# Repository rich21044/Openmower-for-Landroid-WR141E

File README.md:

# Openmower-for-Landroid-WR141E
Taking the hardware developed as part of ClemensElfleins work on Openmower and adapting it to fit a 2019 Landroid WR141E.

This is my first venture into Github so it might get a bit clunky. 
Usual rules apply.. please try to be constructive, I'm learning as I go so if you're going to leave some negative feedback have the grace to tell me why and how I can put it right.

The Openmower project by ClemensElflein started all this for me and I've been so fed up with the performance (or lack thereof) of my Landroid WR141E that I considered selling it and then just buying his kit
however, the Landroid does have cut to edge capability that the Open mower doesnt have and when all is said and done it probably works out at about the same cost.

According to the Gurus on Discord, the firmware in the Landroid is encoded, the data streams between the processors is encoded, the main processor is read locked and the JTAG interface is disabled.
I dont have the knowledge, expertise or equipment to hack into the exiitng Landroid hardware so the plan is to make best use of the Openmower hardware and firmware thats already been developed 
and port it into the Landroid WR141E.

The main thrust of this first stage of the project is to adjust the Openmower motherboard to fit into the available space in the Landroid.

I am also discussing development and asking questions on Discord as @Slartibartfast

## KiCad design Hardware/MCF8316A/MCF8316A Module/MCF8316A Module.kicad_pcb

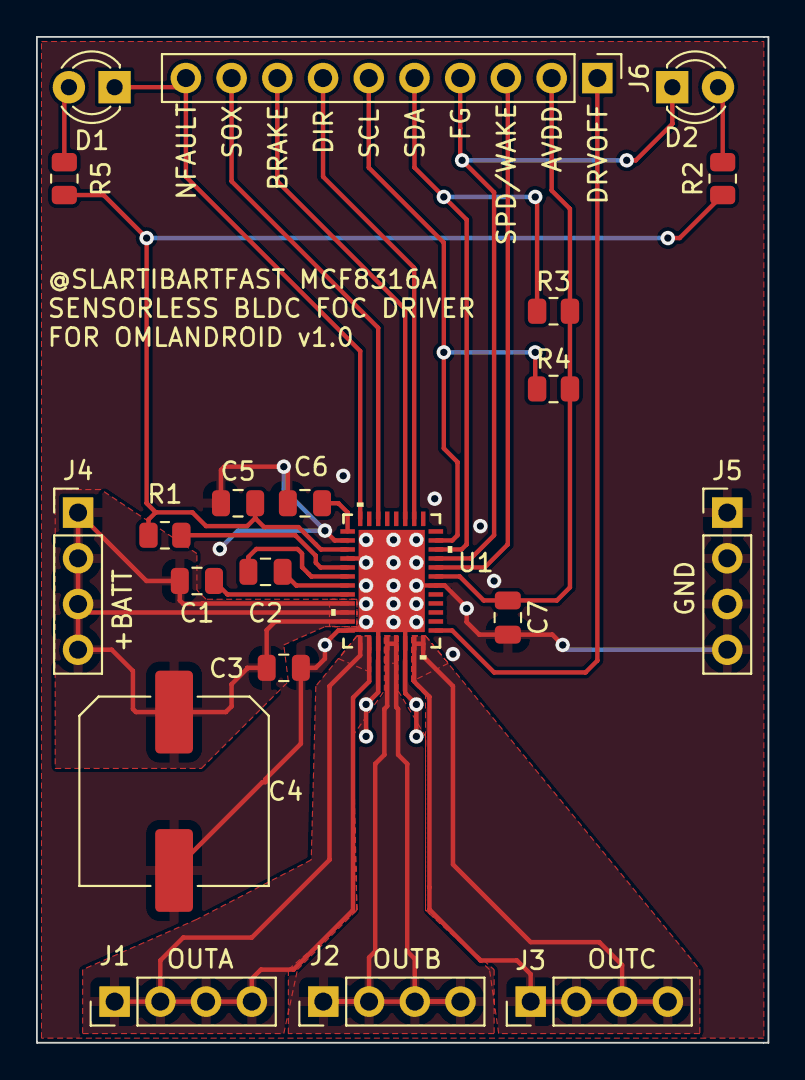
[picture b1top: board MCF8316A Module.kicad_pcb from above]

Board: 2 copper layers, 40.6 x 55.9 mm, 21 parts (0 on the bottom side), 23 nets.

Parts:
C1: 1uF 50v; C_0805_2012Metric
C2: 47nF 50V; C_0805_2012Metric
C3: 0.1uf 50v; C_0805_2012Metric
C4: 330uf 50v; C_Elec_10x10.2
C5: 22uF 10v; C_0805_2012Metric
C6: 1uF 6.3V; C_0805_2012Metric
C7: 1uF 6.3v; C_0805_2012Metric
D1: 3mm Red; LED_D3.0mm
D2: 3mm Grn; LED_D3.0mm
J1, J2, J3, J4, J5: Conn_01x04_Pin; PinHeader_1x04_P2.54mm_Vertical
J6: Conn_01x10_Pin; PinHeader_1x10_P2.54mm_Vertical
R1: 22R; R_0805_2012Metric
R2: 1.54k; R_0805_2012Metric
R3, R4: 5k; R_0805_2012Metric
R5: 1.6k; R_0805_2012Metric
U1: MCF8316A1VRGFR; VQFN40_RGF_TEX

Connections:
+BATT: C1.1, C3.1, C4.1, J4.1, J4.2, J4.3, J4.4, U1.9 (VM), U1.10 (VM), U1.11 (VM)
GND: C3.2, C4.2, C5.2, C6.2, C7.2, J5.1, J5.2, J5.3, J5.4, U1.2 (DGND), U1.4 (GND_BK), U1.12 (PGND), U1.15 (PGND), U1.18 (PGND), U1.26 (AGND), U1.41 (GND)
unnamed: D1.2 (A), R5.2
unnamed: D1.1 (K), J6.10, U1.40 (NFAULT)
unnamed: D2.2 (A), R2.2
unnamed: D2.1 (K), J6.4, U1.29 (FG)
unnamed: J1.1, J1.2, J1.3, J1.4, U1.13 (OUTA), U1.14 (OUTA)
unnamed: J2.1, J2.2, J2.3, J2.4, U1.16 (OUTB), U1.17 (OUTB)
unnamed: J3.1, J3.2, J3.3, J3.4, U1.19 (OUTC), U1.20 (OUTC)
unnamed: J6.1, U1.21 (DRVOFF)
unnamed: C7.1, J6.2, R3.2, R4.2, U1.27 (AVDD)
unnamed: J6.3, U1.28 (SPEED/WAKE)
unnamed: J6.5, R3.1, U1.30 (SDA)
unnamed: J6.6, R4.1, U1.31 (SCL)
unnamed: J6.7, U1.34 (DIR)
unnamed: J6.8, U1.35 (BRAKE)
unnamed: J6.9, U1.38 (SOX)
unnamed: C1.2, U1.8 (CP)
unnamed: C2.1, U1.7 (CPH)
unnamed: C2.2, U1.6 (CPL)
unnamed: C6.1, U1.1 (DVDD)
unnamed: C5.1, R1.1, R2.1, R5.1, U1.3 (FB_BK)
unnamed: R1.2, U1.5 (SW_BK)

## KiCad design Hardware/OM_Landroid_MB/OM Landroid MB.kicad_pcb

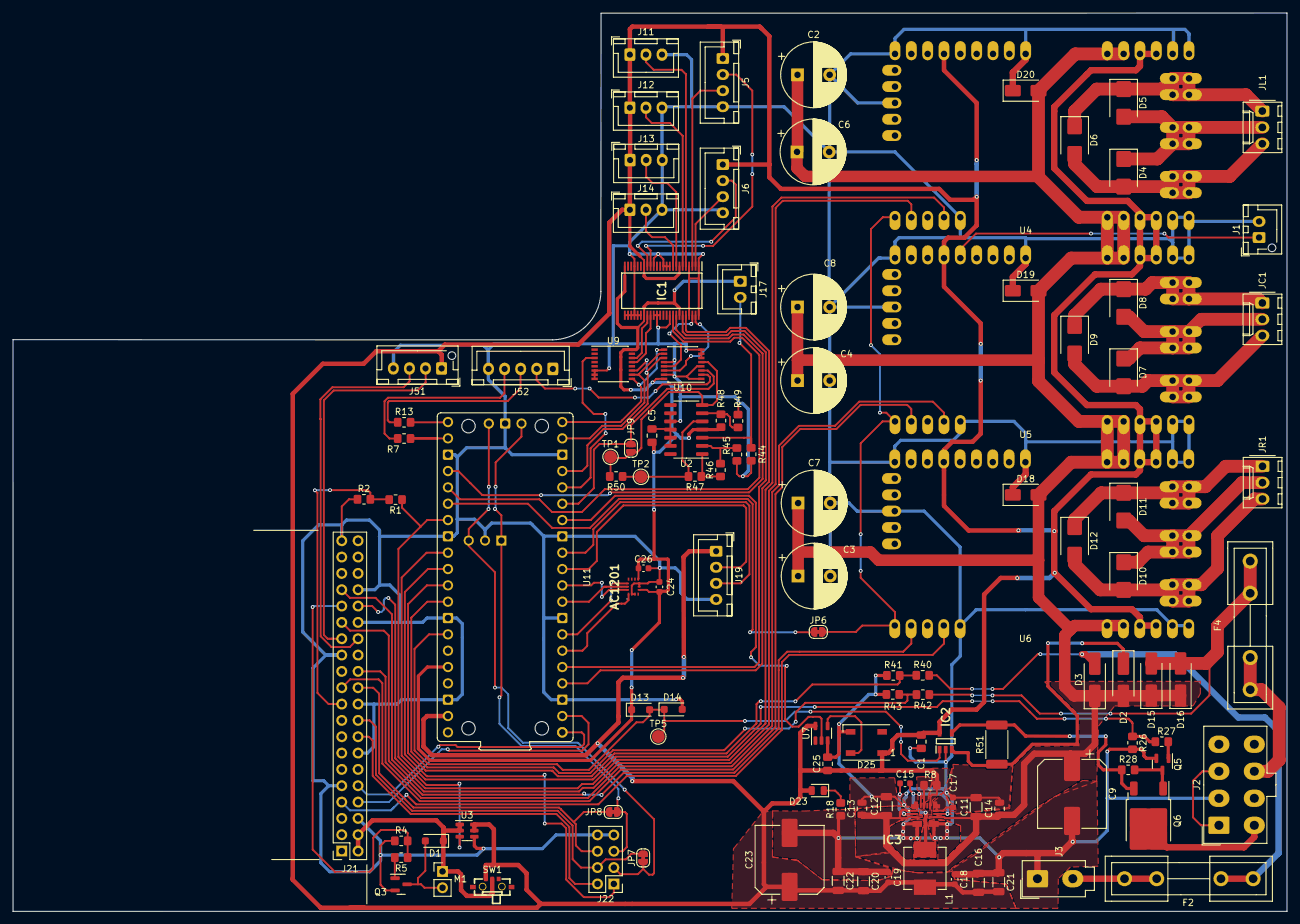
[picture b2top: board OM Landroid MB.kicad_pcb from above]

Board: 2 copper layers, 198.1 x 139.7 mm, 115 parts (0 on the bottom side), 98 nets.

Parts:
AC1201: LSM6DSOTR; LGA-14_2.5X3X0.86_
C1, C5, C25: 100nF; C_0805_2012Metric_Pad1.18x1.45mm_HandSolder
C2, C3, C4, C6, C7, C8: 220uF; CP_Radial_D10.0mm_P5.00mm
C9, C23: 680uF; CP_Elec_10x12.5
C11, C12: 4.7uF; C_1206_3216Metric
C13, C14: 1uF; C_0805_2012Metric
C15, C18, C19, C24, C26: 0.1uF; C_0603_1608Metric
C16, C20, C21, C22: 22uF; C_1206_3216Metric
C17: 2.2uF; C_0603_1608Metric
D1: D_Schottky; D_SOD-123F
D2, D3, D15, D16: D_Schottky; D_SMA_Handsoldering
D4, D5, D6, D7, D8, D9, D10, D11, D12: DNP; D_SMB
D13, D14: DNP; D_SOD-123F
D18, D19, D20: DNP; D_SMA
D23: LED; LED_0805_2012Metric
D25: WS2812B; LED_WS2812B_PLCC4_5.0x5.0mm_P3.2mm
F2, F4: Fuse; Fuseholder5x20_horiz_open_inline_Type-I
IC1: 74ALVC164245DGG,11; SOP50P810X120-48N
IC2: TSC101CILT; SOT95P280X145-5N
IC3: MAX20405AFOF_VY+T; MAX2040
J1: Conn_01x02_Pin; JST_XH_B2B-XH-AM_1x02_P2.50mm_Vertical
J2: Conn_02x04_Top_Bottom; Molex_Mini-Fit_Jr_5566-08A_2x04_P4.20mm_Vertical
J3: Conn_01x02; Molex_Mini-Fit_Jr_5566-02A_2x01_P4.20mm_Vertical
J5, J6, J19: Conn_01x04; JST_XH_B4B-XH-A_1x04_P2.50mm_Vertical
J11, J12, J13, J14: Conn_01x03_Male; JST_XH_B3B-XH-A_1x03_P2.50mm_Vertical
J17: Conn_01x02; JST_XH_B2B-XH-A_1x02_P2.50mm_Vertical
J21: Raspberry_Pi_2_3; PinSocket_2x20_P2.54mm_Vertical
J22: Conn_02x04_Odd_Even; PinHeader_2x04_P2.54mm_Vertical
J51: Conn_01x05_Socket; JST_XH_B4B-XH-AM_1x04_P2.50mm_Vertical
J52: Conn_01x05_Socket; JST_XH_B5B-XH-A_1x05_P2.50mm_Vertical
JC1: Conn_01x03_Pin; Molex_KK-254_AE-6410-03A_1x03_P2.54mm_Vertical
JL1: Conn_01x03_Pin; Molex_KK-254_AE-6410-03A_1x03_P2.54mm_Vertical
JP6, JP7, JP8: SolderJumper_2_Bridged; SolderJumper-2_P1.3mm_Bridged_RoundedPad1.0x1.5mm
JP9: SolderJumper_2_Open; SolderJumper-2_P1.3mm_Open_RoundedPad1.0x1.5mm
JR1: Conn_01x03_Pin; Molex_KK-254_AE-6410-03A_1x03_P2.54mm_Vertical
L1: 4.7uH 5A; L_Vishay_IHLP-2525
M1: Fan; PinHeader_1x02_P2.54mm_Vertical
Q3, Q5: BSS138; SOT-23
Q6: Q_PMOS_GDS; TO-252-2
R1, R2, R4, R26, R28, R40, R42, R48, R50: 10k; R_0805_2012Metric_Pad1.20x1.40mm_HandSolder
R5, R27: 150; R_0805_2012Metric_Pad1.20x1.40mm_HandSolder
R7, R13, R18, R41, R43, R45, R47: 1k; R_0805_2012Metric_Pad1.20x1.40mm_HandSolder
R8: 5k; R_0805_2012Metric_Pad1.20x1.40mm_HandSolder
R44, R46: 47k; R_0805_2012Metric_Pad1.20x1.40mm_HandSolder
R49: 4k7; R_0805_2012Metric_Pad1.20x1.40mm_HandSolder
R51: 0.003R; R_2512_6332Metric_Pad1.40x3.35mm_HandSolder
SW1: MK-11C04-G013; SW-SMD_MK-11C04-G013
TP1, TP2, TP5: TestPoint; TestPoint_Pad_D2.0mm
U2: MCP604; SOIC-14_3.9x8.7mm_P1.27mm
U3: SIP32509DT; SOT-23-6
U4, U5, U6: xESC2
U7: SN74LV1T34DBV; SOT-23-5
U9, U10: 74HC4051; SSOP-16_4.4x5.2mm_P0.65mm
U11: Pico; Raspberry_Pi_Pico_THT

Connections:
+3V3: AC1201.5 (VDDIO), AC1201.8 (VDD), C5.2, C24.1, C26.1, D13.1 (K), IC1.24 (2DIR), IC1.31 (VCC(A)_1), IC1.42 (VCC(A)_2), J17.1, R48.2, U2.4 (V+), U9.16 (VCC), U10.16 (VCC), U11.36 (3V3)
+5V: C1.1, C16.2, C18.2, C19.2, C20.2, C21.2, C22.2, C23.1, C25.1, D23.2 (A), D25.1 (VDD), IC1.7 (VCC(B)_1), IC1.18 (VCC(B)_2), IC2.5 (VCC), IC3.13 (OUT), J5.1, J6.1, J11.1, J12.1, J13.1, J14.1, J19.1, J51.1, L1.2, R8.2, SW1.1, U3.5 (VIN), U3.6 (VIN), U4.5V, U5.5V, U6.5V, U7.5 (VCC), U11.39 (VSYS)
/CHARGE_CURRENT: D13.2 (A), D14.1 (K), IC2.1 (OUT), TP5.1, U11.34 (GPIO28_ADC2)
/ESCs/ESC_SHUTDOWN: JP6.1 (A), U11.26 (GPIO20)
/ESCs/MC_PHASE_U: D7.2 (A2), D9.2 (A2), JC1.3, U5.U
/ESCs/MC_PHASE_V: D7.1 (A1), D8.2 (A2), JC1.2, U5.V
/ESCs/MC_PHASE_W: D8.1 (A1), D9.1 (A1), JC1.1, U5.W
/ESCs/MC_RX: J21.24 (~CE0/GPIO8), U5.14 (NCS/RX)
/ESCs/MC_TEMP: J1.1, U5.3 (TEMPERATURE)
/ESCs/MC_TX: J21.21 (MISO0/GPIO9), U5.12 (MOSI/TX)
/ESCs/ML_PHASE_U: D4.2 (A2), D6.2 (A2), JL1.3, U4.U
/ESCs/ML_PHASE_V: D4.1 (A1), D5.2 (A2), JL1.2, U4.V
/ESCs/ML_PHASE_W: D5.1 (A1), D6.1 (A1), JL1.1, U4.W
/ESCs/ML_RX: J21.32 (PWM0/GPIO12), U4.14 (NCS/RX)
/ESCs/ML_TX: J21.33 (PWM1/GPIO13), U4.12 (MOSI/TX)
/ESCs/MR_PHASE_U: D10.2 (A2), D12.2 (A2), JR1.3, U6.U
/ESCs/MR_PHASE_V: D10.1 (A1), D11.2 (A2), JR1.2, U6.V
/ESCs/MR_PHASE_W: D11.1 (A1), D12.1 (A1), JR1.1, U6.W
/ESCs/MR_RX: J21.7 (GCLK0/GPIO4), U6.14 (NCS/RX)
/ESCs/MR_TX: J21.29 (GCLK1/GPIO5), U6.12 (MOSI/TX)
/IMU/MISO: AC1201.1 (SDO/SA0), U11.6 (GPIO4)
/IMU/MOSI: AC1201.14 (SDA), U11.10 (GPIO7)
/IMU/SCK: AC1201.13 (SCL), U11.9 (GPIO6)
/IMU/~CS: AC1201.12 (CS), U11.7 (GPIO5)
/RAIN_DETECTED: JP9.1 (A), R50.2, TP1.1, U2.7, U10.5 (A5)
/RaspberryPi/PICO_RESET: J22.1, U11.30 (RUN)
/RaspberryPi/PICO_SWCLK: J22.5, JP8.1 (A), U11.41 (SWCLK)
/RaspberryPi/PICO_SWDIO: J22.3, JP7.1 (A), U11.43 (SWDIO)
/RaspberryPi/POWER_EN: R1.1, U3.3 (ENABLE), U11.27 (GPIO21)
/RaspberryPi/RASPI_FAN_ON: J21.31 (GCLK2/GPIO6), R4.2, R5.1
/RaspberryPi/RASPI_POWER: D1.1 (K), J21.2 (5V), J21.4 (5V), M1.1 (+), SW1.C, U3.1 (VOUT), U3.2 (VOUT)
/RaspberryPi/UART0_RXD: J21.10 (GPIO15/RXD), U11.1 (GPIO0)
/RaspberryPi/UART0_TXD: J21.8 (GPIO14/TXD), U11.2 (GPIO1)
/RaspberryPi/UART1_RXD: J21.28 (ID_SC/GPIO1), J51.3
/RaspberryPi/UART1_TXD: J21.27 (ID_SD/GPIO0), J51.2
/RobotConnectors/CHARGE_SHUNT_MINUS: IC2.4 (VM), Q6.3 (S), R28.1, R51.2
/RobotConnectors/CHARGE_SHUNT_PLUS: D2.1 (K), IC2.3 (VP), R51.1
/RobotConnectors/ENABLE_CHARGE: R26.1, R27.1, U11.29 (GPIO22)
/RobotConnectors/HALL_SWITCH_1: IC1.41 (1A4), U11.24 (GPIO18)
/RobotConnectors/HALL_SWITCH_1_5V: IC1.8 (1B4), J13.2
/RobotConnectors/HALL_SWITCH_2: IC1.40 (1A5), U11.25 (GPIO19)
/RobotConnectors/HALL_SWITCH_2_5V: IC1.9 (1B5), J14.2
/RobotConnectors/HALL_SWITCH_3: IC1.43 (1A3), U11.5 (GPIO3)
/RobotConnectors/HALL_SWITCH_3_5V: IC1.6 (1B3), J12.2
/RobotConnectors/HALL_SWITCH_4: IC1.44 (1A2), U11.4 (GPIO2)
/RobotConnectors/HALL_SWITCH_4_5V: IC1.5 (1B2), J11.2
/RobotConnectors/LED_RX: J19.2, U11.11 (GPIO8)
/RobotConnectors/LED_TX: J19.3, U11.12 (GPIO9)
/RobotConnectors/MosfetSwitch/VOUT: J2.5, Q6.2 (D)
/RobotConnectors/RAIN-: J17.2, R44.2, U2.3 (+)
/RobotConnectors/SOUND_BUSY: J52.2, U10.2 (A6)
/RobotConnectors/SOUND_RX: R13.2, U11.21 (GPIO16)
/RobotConnectors/SOUND_TX: R7.2, U11.22 (GPIO17)
/RobotConnectors/USS_1_ECHO: IC1.46 (1A1), U10.13 (A0)
/RobotConnectors/USS_1_ECHO_5V: IC1.3 (1B1), J5.3
/RobotConnectors/USS_1_TRIGGER: IC1.33 (2A2), U9.13 (A0)
/RobotConnectors/USS_1_TRIGGER_5V: IC1.16 (2B2), J5.2
/RobotConnectors/USS_2_ECHO: IC1.47 (1A0), U10.14 (A1)
/RobotConnectors/USS_2_ECHO_5V: IC1.2 (1B0), J6.3
/RobotConnectors/USS_2_TRIGGER: IC1.32 (2A3), U9.14 (A1)
/RobotConnectors/USS_2_TRIGGER_5V: IC1.17 (2B3), J6.2
/RobotConnectors/V_BATTERY: D15.2 (A), D16.2 (A), F4.2, R42.2
/RobotConnectors/V_CHARGE: D3.2 (A), F2.1, R40.2
/pico/MUX_ADDRESS_0: U9.11 (S0), U10.11 (S0), U11.17 (GPIO13)
/pico/MUX_ADDRESS_1: U9.10 (S1), U10.10 (S1), U11.19 (GPIO14)
/pico/MUX_ADDRESS_2: U9.9 (S2), U10.9 (S2), U11.20 (GPIO15)
/pico/MUX_INPUT: JP9.2 (B), U10.3 (A), U11.15 (GPIO11)
/pico/MUX_OUTPUT: U9.3 (A), U11.16 (GPIO12)
/pico/V_CHARGE: R40.1, R41.2, U11.31 (GPIO26_ADC0)
/pico/V_IN: R42.1, R43.2, U11.32 (GPIO27_ADC1)
GND: AC1201.2 (SDX), AC1201.3 (SCX), AC1201.6 (GND_1), AC1201.7 (GND_2), C1.2, C2.2, C3.2, C4.2, C5.1, C6.2, C7.2, C8.2, C9.2, C11.2, C12.2, C13.2, C14.2, C16.1, C17.2, C18.1, C19.1, C20.1, C21.1, C22.1, C23.2, C24.2, C25.2, C26.2, D14.2 (A), D18.1 (A1), D19.1 (A1), D20.1 (A1), D25.3 (VSS), IC1.1 (1DIR), IC1.4 (GND_1), IC1.10 (GND_2), IC1.11 (1B6), IC1.12 (1B7), IC1.15 (GND_3), IC1.21 (GND_4), IC1.25 (~2OE), IC1.26 (2A7), IC1.27 (2A6), IC1.28 (GND_5), IC1.29 (2A5), IC1.30 (2A4), IC1.34 (GND_6), IC1.35 (2A1), IC1.36 (2A0), IC1.39 (GND_7), IC1.45 (GND_8), IC1.48 (~1OE), IC2.2 (GND), IC3.4 (PGND_1), IC3.5 (PGND_2), IC3.7 (PGND_3), IC3.8 (PGND_4), J1.2, J2.2, J3.1, J5.4, J6.4, J11.3, J12.3, J13.3, J14.3, J19.4, J21.6 (GND), J21.9 (GND), J21.14 (GND), J21.20 (GND), J21.25 (GND), J21.30 (GND), J21.34 (GND), J21.39 (GND), J22.7, J22.8, J51.4, J52.5, Q3.2 (S), Q5.2 (S), R2.1, R4.1, R18.1, R26.2, R41.1, R43.1, R44.1, R45.1, R49.2, U2.9 (-), U2.10 (+), U2.11 (V-), U2.12 (+), U2.13 (-), U3.4 (GND), U4.GND, U5.GND, U6.GND, U7.3 (GND), U9.6 (~E), U9.7 (VEE), U9.8 (GND), U10.1 (A4), U10.4 (A7), U10.6 (~E), U10.7 (VEE), U10.8 (GND), U10.12 (A3), U10.15 (A2), U11.3 (GND), U11.8 (GND), U11.13 (GND), U11.18 (GND), U11.23 (GND), U11.28 (GND), U11.33 (AGND), U11.38 (GND), U11.42 (SWGND)
unnamed: D1.2 (A), M1.2 (-), Q3.3 (D)
unnamed: D23.1 (K), R18.2
unnamed: D25.4 (DIN), U7.4 (Y)
unnamed: C17.1, IC3.11 (BIAS), IC3.12 (FB_1)
unnamed: C15.1, IC3.2 (BST)
unnamed: IC3.10 (GND), IC3.16 (SYNC)
unnamed: C15.2, IC3.6 (LX_1), L1.1
unnamed: IC3.15 (PGOOD), R8.1
unnamed: J2.1, J2.3
unnamed: F4.1, J2.7
unnamed: F2.2, J3.2
unnamed: J21.16 (GPIO23), J22.2
unnamed: J21.18 (GPIO24), J22.4, JP7.2 (B)
unnamed: J21.22 (GPIO25), J22.6, JP8.2 (B)
unnamed: J21.19 (MOSI0/GPIO10), R1.2, R2.2
unnamed: J52.3, R13.1
unnamed: J52.4, R7.1
unnamed: JP6.2 (B), U4.11 (MISO), U5.11 (MISO), U6.11 (MISO)
unnamed: Q3.1 (G), R5.2
unnamed: Q5.3 (D), Q6.1 (G), R28.2
unnamed: Q5.1 (G), R27.2
unnamed: R46.1, R47.1, U2.1
unnamed: R45.2, R46.2, U2.2 (-)
unnamed: R47.2, R50.1, TP2.1, U2.5 (+)
unnamed: R48.1, R49.1, U2.6 (-)
unnamed: U7.2 (A), U11.14 (GPIO10)
V_BATT: C2.1, C3.1, C4.1, C6.1, C7.1, C8.1, C9.1, C11.1, C12.1, C13.1, C14.1, D2.2 (A), D3.1 (K), D15.1 (K), D16.1 (K), D18.2 (A2), D19.2 (A2), D20.2 (A2), IC3.1 (EN), IC3.3 (SUP_1), IC3.9 (SUP_2), U4.VM (VIN), U5.VM (VIN), U6.VM (VIN)

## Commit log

2023-11-07 Create test
2023-11-08 Create Changelog
2023-11-08 Update Changelog
2023-11-09 Add files via upload
    Updates for Schematic and PCB with additional footprint for the TE-179839 3 pin connector which matches the original motor connectors - thus avoiding the need to change these when installing the new 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
2023-11-09 Update Changelog
    9 Nov 2023 update
2023-11-10 Update Changelog
    10 Nov Update
2023-11-10 Schematic update
    Getting to grips with Github desktop...I worked out that I'd changed the PCB but had forgotten to update the schematic file for Kicad for the connectors ....so there was a disconnect :)
2023-11-12 Weekend progress
2023-11-14 Daily update
2023-11-22 Finished Mainboard
    Finished Mainboard redesign for OM Landroid
2023-11-26 Updates and revisions to charging connections
2023-11-29 Changes to align BOM with board
    Changes were needed to align the BOM content with the board and to reflect component availability from Digikey
2023-11-30 MCF8316A test board produced and sent to PCBway
2023-12-05 MCF8316a driver board photo added
    Fresh from PCBway
2024-04-18 Create Documents
